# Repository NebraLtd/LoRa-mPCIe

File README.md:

# LoRa-mPCIe
Open source mPCIe LoRa® concentrators from Nebra

## Branches

This repo contains a number of branches with different versions of the LoRa mPCIe hardware as set out below.

### Main

The [main branch of this repo](https://github.com/NebraLtd/LoRa-mPCIe) contains the initial design of the SX1302/3 concentrator but it is based on the original version of the Semtech reference design. It is therefore outdated and is here just for reference purposes. **This hardware has not been verified with prototypes. We do not recommend you use this design.**

### v1.1

The [v1.1 branch of this repo](https://github.com/NebraLtd/LoRa-mPCIe/tree/v1.1) is the latest version of the SX1302/3 based LoRa concentrator design, based on the v3 Semtech Corecell reference design.

There are multiple variants (USB/SPI versions, GNSS/no-GNSS versions and different frequency options). Visit the [v1.1 VARIANTS file](https://github.com/NebraLtd/LoRa-mPCIe/blob/v1.1/VARIANTS.md) for more information on the different hardware versions and how to produce them.

### v1.2
The development can be followed on the v1.2 branch but keeping the branch unmerged to master would create issues as branches generally accepted as unstable. Also the design will be ended with v1.2 from various reasons (Branding issues with Semtech, semantic versioning does not work in hardware design as in software development)

The variant files also can be observed in the Output's folder under their respective folders.

Note: Successor of this design will appear soon in another repo.

### 470/433

In the future, we will have our 470 MHz and 433 MHz designs available as well. As the design differs considerably from the 868/915 versions it may be in a separate branch.

## Open Source Hardware Certification

We are proud to announce that the Nebra LoRa mPCIe Concentrator project is certified as Open Source Hardware by the Open Source Hardware Association ([OSHWA](https://www.oshwa.org/)). The registration number for this project is [UK000026](https://certification.oshwa.org/uk000026.html).

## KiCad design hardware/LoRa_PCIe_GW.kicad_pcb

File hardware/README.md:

# LoRa Gateway mini-PCIe Module (SX1302/3) KiCad Open Source Design

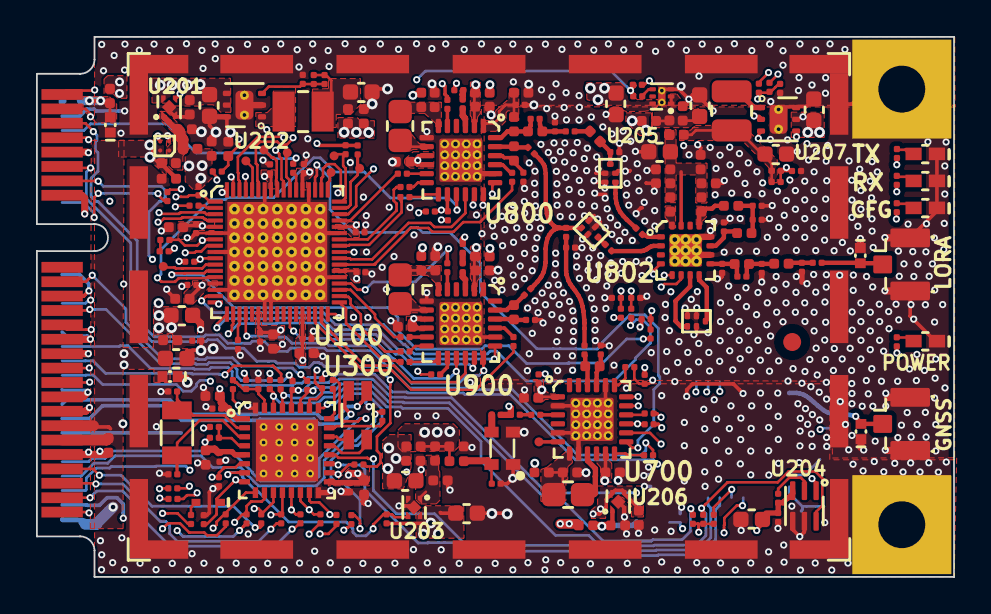
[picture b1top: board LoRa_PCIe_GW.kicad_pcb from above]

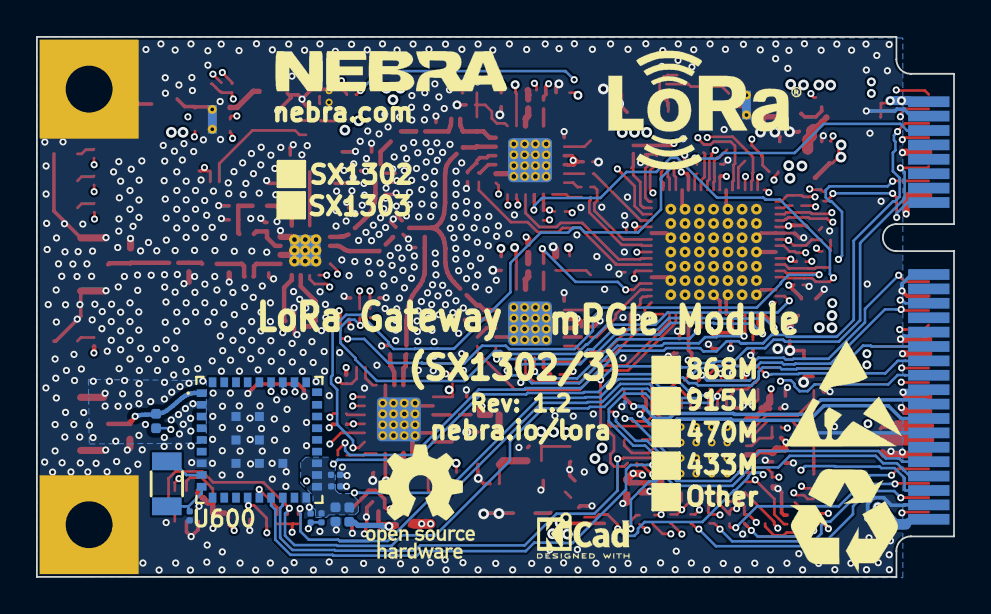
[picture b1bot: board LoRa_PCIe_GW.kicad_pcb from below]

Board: 6 copper layers, 50.9 x 30.0 mm, 269 parts (16 on the bottom side), 190 nets.

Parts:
A1, A2: U.FL; U.FL-R-SMT_Hirose
C100, C102, C103, C105, C106, C107, C108, C109, C110, C600, C602, C838: 100nF; ccer_201_smd_small
C101, C104, C111, C112, C200, C201, C202, C226, C816, C916: 1uF; ccer_402_smd_small
C203: 10uF; ccer_603_smd_small
C204, C822: 4.7uF; ccer_603_smd_small
C205, C207, C211, C212, C222, C305: NC; ccer_603_smd_small
C206, C215, C308: 47uF; ccer_603_smd_small
C208, C210, C216, C220, C221, C312, C818, C918: 100nF; ccer_402_smd_small
C209, C213, C225, C716, C717, C718: NC; ccer_402_smd_small
C214, C223, C309, C708, C710, C711, C712, C713, C827: NC; ccer_201_smd_small
C224: 4.7uF; ccer_402_smd_small
C231: 22pF; ccer_201_smd_small
C301, C307, C310: NC; rlc_402_smd_small
C302, C303, C304, C306, C311: NC; rlc_201_smd_small
C601, C802: 47pF; ccer_201_smd_small
C801: 47nF; ccer_402_smd_small
C804, C831, C832: 3.3pF; ccer_201_smd_small
C805: 5.6pF; ccer_201_smd_small
C806: 39pF; ccer_201_smd_small
C807: 2.2pF; ccer_201_smd_small
C808, C828, C908: 10pF; ccer_201_smd_small
C809, C815, C819, C820, C821, C834: 56pF; ccer_201_smd_small
C811, C812, C911, C912: 3.6pF; ccer_201_smd_small
C817, C917: 470nF; ccer_402_smd_small
C823: 10nF; ccer_402_smd_small
C824: 1nF; ccer_402_smd_small
C825, C826: 100pF; ccer_402_smd_small
C829: 1.3pF; ccer_201_smd_small
C830: 1.5pF; ccer_201_smd_small
C833: 2.7pF; ccer_201_smd_small
D101: BAT54; SOD523
D301: NC; SLP1006P2T
D302: 20V; SLP1006P2T
D600, D801: SLP1006P2T
FB203, FB207, FB208, FB211, FB212, FB302, FB801: Ferrite beads; rlc_402_smd_small
FB205, FB206, FB301: NC; rlc_402_smd_small
Fiducial1: NC; fiducial_mark_signal_top
H1, H2: NC; MountingHole
L200: 2.2uH; LQM2HPN2R2MJ0L
L201: NC; LQM2HPN2R2MJ0L
L300: NC; IND_744232090
L601, L801: 47nH; rlc_402_smd_small
L706, L708, L808, L908: NC; rlc_402_smd_small
L707: NC; rlc_805_smd_small
L803: 2.5nH; rlc_402_smd_small
L804: 4.7nH; rlc_402_smd_small
L806, L906: 12nH; rlc_402_smd_small
L807, L907: 15uH; rlc_805_smd_small
L809: 6.8nH; rlc_402_smd_small
L810: 3.0nH; rlc_402_smd_small
L811: 7.5nH; rlc_402_smd_small
L812: 1.2nH; rlc_402_smd_small
L813, L814: 5.6nH; rlc_402_smd_small
LED1: RED; CD1005-0402-RED
LED2, LED4: GREEN; CD1005-0402
LED3: YELLOW; CD1005-0402-YELLOW
Logo1: NC; Logo_Recycling
Logo2: NC; Logo_ESD
Logo3: NC; Logo_LoRa
Logo4: NC; Logo_KiCad
Logo5: NC; nebra
Logo6: NC; open_source
PCIe_1: NC; PCIeMini-GF-2D-800-1K-S52
Q300, Q600: NC; XTAL_3215_SMD
R101, R103, R107: 47k; rlc_201_smd_small
R102, R301, R302, R308, R309, R316, R317, R318, R319, R326, R331, R332, R333, R334: 100R; rlc_201_smd_small
R104, R105: 680R; rlc_201_smd_small
R106: 820R; rlc_201_smd_small
R108, R600: 10R; rlc_201_smd_small
R109, R110, R111, R112, R113, R114, R115, R120, R121, R122, R123, R124, R125, R200, R602, R815: 0R; rlc_201_smd_small
R116, R117, R203, R206, R601: 4.7k; rlc_201_smd_small
R201: 47K; rlc_201_smd_small
R204, R205, R207, R209, R210, R211, R212, R213, R300, R303, R304, R305, R306, R307, R312, R314, R315, R320, R321, R322, R323, R325, R327, R701, R702, R703, R704, R705, R713: NC; rlc_201_smd_small
R208, R330, R805, R807, R809: 1k; rlc_201_smd_small
R215: NC; rlc_402_smd_small
R221, R222, R813, R913: 0R; rlc_402_smd_small
R231, R232: 182K; rlc_201_smd_small
R801, R901: 220R; rlc_201_smd_small
RF1: Shield Frame; SMS-458F_Shield
RF2: Shield Cover; SMS-458C_Shield_cover
TP1, TP3, TP5, TP6, TP7, TP9, TP10, TP11: NC; PIN_SMD
U100: SX1303; vqfn68_7x7mm
U200: NC; DSBGA-4
U201: 3V3; UDFN4_1x1mm
U202: TPS62260DRV; DRV0006A_V
U203, U206: NC; UDFN4_1x1mm
U204: NC; UDFN-6L_2X2mm
U205: NC; XDFN6_1.2X1.2mm
U207: NC; DRV0006A_V
U300: NC; UFQFPN32_5x5mm
U600: EVA-M8M-0; LGA43R65P9X9_700X700X116
U700: NC; vqfn24_4x4mm
U800, U900: SX1250; vqfn24_4x4mm
U801, U803, U805: SAW Filter; QCS5P_1.4x1.1mm
U802: SKY66423-11; SKY66420_16P_3x3mm
Y800: TCXO; TCXO_2x1_6mm

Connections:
/CONFIG_OK: R105.2, U100.66
/GPIO(9): TP9.1, U100.52
/GPIO(10): R116.1, TP10.1, U100.51
/GPIO(11): R117.1, TP11.1, U100.50
/RADIO_CTRL_(1): TP7.1, U100.11
/RX_ON: R106.2, U100.59
/SCH1/ANT_RF1: C830.2, C831.2, L813.1, U802.9
/SCH1/ANT_RF2: C830.1, C832.1, L813.2, L814.1
/SCH1/ANT_RF3: C833.1, C834.1, L814.2
/SCH1/ANT_RF4: A1.1, C834.2, D801.1
/SCH1/CSD: C819.2, R805.2, U802.4
/SCH1/LNAFLT_RF: U802.8, U803.1
/SCH1/LNAIN_RF: U802.7, U803.4
/SCH1/PA_ON: C821.2, R809.2, U802.5
/SCH1/PA_RF1: L809.1, L810.1, U802.13
/SCH1/PA_RF2: C827.2, C828.2, L810.2, L811.1
/SCH1/PA_RF3: C829.2, L811.2, U802.11
/SCH1/RXTX_SW: C820.2, R807.2, U802.6
/SCH1/RX_RF: C815.2, U802.2
/SCH1/RX_RF1: C815.1, U801.1
/SCH1/RX_RF2: C710.1, C811.1, C911.1, U801.4
/SCH1/SX1250_RFI1_N: C811.2, L806.2, U800.23
/SCH1/SX1250_RFI1_P: C812.2, L806.1, U800.22
/SCH1/SX1250_RFI2_N: C911.2, L906.2, U900.23
/SCH1/SX1250_RFI2_P: C912.2, L906.1, U900.22
/SCH1/SX1261_RFI: C710.2, C711.1, C713.2
/SCH1/SX1261_RFI_N: C711.2, L706.2, U700.22
/SCH1/SX1261_RFI_P: C712.2, L706.1, U700.21
/SCH1/TCXO_32M_O: R701.2, R801.2, R815.1, R901.2
/SCH1/TX_RF: C809.2, U802.1
/SCH1/TX_RF1: C804.2, L801.1, L803.1, U800.24
/SCH1/TX_RF2: C804.1, C805.2, C806.2, L803.2
/SCH1/TX_RF3: C807.2, L804.2, U805.1
/SCH1/TX_RF4: C809.1, U805.4
/SCH1/VR_PA: C801.2, C802.2, L801.2, U800.1
/SCH2/DEBUG_JTCK-SWCLK: R322.2, U300.24
/SCH2/DEBUG_JTMS-SWDIO: R323.2, U300.23
/SCH2/MCU_BOOT0: R304.2, R321.1, R325.1, U300.31
/SCH2/MCU_NRESET: R300.1, R320.1, U300.4
/SCH2/OSC32_IN: C303.1, Q300.2, U300.2
/SCH2/OSC32_OUT: C304.2, Q300.1, U300.3
/SCH2/RADIO_A_CLK_32M_MCU: R303.2, R305.1, U300.6
/SCH2/USB_DN: L300.3, PCIe_1.36
/SCH2/USB_DP: L300.2, PCIe_1.38
/SCH2/VCC5V_IN: D301.1, FB301.1, PCIe_1.2
/SCH3/U205_EN: R207.2, U205.4
/SCH3/U206_EN: R204.2, U207.4
/SCH4/GNSS_RF: A2.1, D600.1, L601.2, U600.1
/TX_ON: R104.2, U100.63
GND: A1.2, A1.3, A2.2, A2.3, C101.1, C102.1, C103.1, C104.1, C105.1, C106.1, C107.1, C108.1, C109.1, C110.1, C111.1, C112.1, C200.2, C201.2, C202.2, C203.2, C204.2, C205.2, C206.2, C207.2, C208.1, C209.2, C210.1, C211.2, C212.2, C213.2, C215.2, C216.1, C220.1, C221.1, C222.2, C223.2, C224.2, C225.2, C226.2, C301.1, C302.2, C303.2, C304.1, C305.2, C306.2, C307.1, C308.2, C309.2, C310.1, C311.2, C312.2, C600.1, C601.1, C602.1, C712.1, C713.1, C716.1, C717.1, C718.1, C801.1, C802.1, C805.1, C807.1, C812.1, C816.1, C817.1, C818.1, C819.1, C820.1, C821.1, C822.1, C823.1, C824.1, C825.1, C826.1, C827.1, C828.1, C829.1, C831.1, C832.2, C833.2, C838.1, C912.1, C916.1, C917.1, C918.1, D301.2, D302.2, D600.2, D801.2, H1.1, H2.1, LED1.2, LED2.2, LED3.2, LED4.2, PCIe_1.4, PCIe_1.9, PCIe_1.15, PCIe_1.18, PCIe_1.21, PCIe_1.26, PCIe_1.27, PCIe_1.29, PCIe_1.34, PCIe_1.35, PCIe_1.37, PCIe_1.40, PCIe_1.43, PCIe_1.50, R101.1, R109.1, R210.1, R212.1, R232.1, R304.1, R305.2, R602.1, RF1.1, U100.6, U100.9, U100.15, U100.24, U100.25, U100.39, U100.46, U100.55, U100.62, U100.69, U200.B1, U201.2, U201.5, U202.2, U202.6, U202.7, U203.2, U203.5, U204.4, U204.5, U205.3, U205.7, U206.2, U206.5, U207.6, U207.7, U300.16, U300.32, U300.33, U600.2, U600.7, U600.18, U600.37, U600.38, U600.39, U600.40, U600.41, U600.42, U600.43, U700.2, U700.5, U700.8, U700.20, U700.25, U800.7, U800.20, U800.25, U801.2, U801.3, U801.5, U802.10, U802.12, U802.17, U803.2, U803.3, U803.5, U805.2, U805.3, U805.5, U900.7, U900.20, U900.25, Y800.1, Y800.2
GNSS_STANDBY: R332.1, U300.25, U600.13
GPIO(6): R326.2, U100.57
HOST_CSN: R103.1, R319.1, U100.1, U300.10
HOST_MISO: R102.2, R317.1, R704.2, U300.12
HOST_MOSI: R318.1, U100.3, U300.13, U700.17
HOST_SCK: R316.1, U100.4, U300.11, U700.18
HOST_UART_RX: R334.1, U300.20, U600.16
HOST_UART_TX: R333.1, U300.19, U600.15
I2C_SCL: R206.1, R308.2, U204.1, U300.29, U600.29
I2C_SDA: R203.1, R309.2, U204.6, U300.30, U600.30
unnamed: C100.2, R108.1
unnamed: C200.1, R200.2, U200.B2, U201.3
unnamed: C202.1, FB207.1, R215.1, U200.A1, U201.1
unnamed: C203.1, C231.2, FB208.1, L200.2, R231.2
unnamed: C211.1, C214.2, FB206.1, L201.2, R211.2
unnamed: C213.1, FB205.1, U203.1
unnamed: C214.1, R211.1, R212.2, U207.3
unnamed: C226.1, FB212.1, R221.1, U206.1
unnamed: C231.1, R231.1, R232.2, U202.3
unnamed: C601.2, L601.1, R600.2
unnamed: C708.1, U700.3
unnamed: C708.2, R701.1
unnamed: C716.2, C718.2, L708.2, R702.1, R703.1, R713.2, U700.1, U700.10, U700.11
unnamed: C717.2, L707.1, L708.1, U700.7
unnamed: C806.1, L804.1
unnamed: C808.1, U800.3
unnamed: C808.2, R801.1
unnamed: C816.2, C818.2, L808.2, R813.2, U800.2, U800.9, U800.10
unnamed: C817.2, L807.1, L808.1, U800.6
unnamed: C838.2, FB801.2, Y800.4
unnamed: C908.1, U900.3
unnamed: C908.2, R901.1
unnamed: C916.2, C918.2, L908.2, R913.2, U900.2, U900.9, U900.10
unnamed: C917.2, L907.1, L908.1, U900.6
unnamed: L200.1, U202.1
unnamed: L201.1, U207.1
unnamed: L300.1, U300.22
unnamed: L300.4, U300.21
unnamed: L707.2, U700.9
unnamed: L807.2, U800.8
unnamed: L812.1, U802.16
unnamed: L907.2, U900.8
unnamed: LED1.1, R104.1
unnamed: LED2.1, R105.1
unnamed: LED3.1, R106.1
unnamed: LED4.1, R208.2
unnamed: PCIe_1.1, R306.1
unnamed: PCIe_1.3, R314.1
unnamed: PCIe_1.5, R307.1
unnamed: PCIe_1.6, R326.1
unnamed: PCIe_1.7, R312.1
unnamed: PCIe_1.11, R315.1
unnamed: PCIe_1.13, R320.2
unnamed: PCIe_1.16, R301.1
unnamed: PCIe_1.19, R330.2
unnamed: PCIe_1.22, R302.1
unnamed: PCIe_1.23, R331.2
unnamed: PCIe_1.25, R332.2
unnamed: PCIe_1.28, R327.1
unnamed: PCIe_1.30, R308.1
unnamed: PCIe_1.31, R333.2
unnamed: PCIe_1.32, R309.1
unnamed: PCIe_1.33, R334.2
unnamed: PCIe_1.44, R322.1
unnamed: PCIe_1.45, R316.2
unnamed: PCIe_1.46, R323.1
unnamed: PCIe_1.47, R317.2
unnamed: PCIe_1.48, R325.2
unnamed: PCIe_1.49, R318.2
unnamed: PCIe_1.51, R319.2
unnamed: Q600.1, R602.2, U600.9
unnamed: Q600.2, U600.8
unnamed: R102.1, U100.2
unnamed: R109.2, U100.20
unnamed: R110.1, U100.44
unnamed: R111.1, U100.45
unnamed: R112.1, U100.49
unnamed: R113.1, U100.41
unnamed: R114.1, U100.48
unnamed: R115.1, U100.43
unnamed: R120.1, U100.35
unnamed: R121.1, U100.36
unnamed: R122.1, U100.38
unnamed: R123.2, U100.32
unnamed: R124.1, U100.37
unnamed: R125.2, U100.34
unnamed: R205.1, U204.2
unnamed: R209.2, R210.2, R213.2, U207.2
unnamed: R704.1, U700.16
unnamed: R705.1, U700.19
unnamed: R815.2, Y800.3
unnamed: TP1.1, U100.64
unnamed: TP3.1, U100.60
unnamed: TP5.1, U100.58
unnamed: TP6.1, U700.6
POWER_EN: R201.2, R301.2, U203.3, U300.7
PPS: R330.1, U100.8, U300.27, U600.31
RADIO_A_CLK_32M: R115.2, R303.1, U800.14
RADIO_A_CLK_O: R114.2, U800.11
RADIO_A_CSN: U100.68, U800.19
RADIO_A_IQ(0): R110.2, U800.13
RADIO_A_IQ(1): R111.2, U800.12
RADIO_A_IQ(2): R112.2, U800.5
RADIO_A_IQ(3): R113.2, U800.21
RADIO_A_MISO: U100.42, U800.16
RADIO_A_MOSI: U100.67, U800.17
RADIO_A_NRESET: U100.13, U800.15
RADIO_A_SCK: U100.65, U800.18
RADIO_B_CLK_32M: R125.1, U900.14
RADIO_B_CLK_O: R124.2, U900.11
RADIO_B_CSN: U100.18, U900.19
RADIO_B_IQ(0): R120.2, U900.13
RADIO_B_IQ(1): R121.2, U900.12
RADIO_B_IQ(2): R122.2, U900.5
RADIO_B_IQ(3): R123.1, U900.21
RADIO_B_MISO: U100.33, U900.16
RADIO_B_MOSI: U100.19, U900.17
RADIO_B_NRESET: U100.28, U900.15
RADIO_B_SCK: U100.21, U900.18
SX1261_BUSY: R306.2, U300.9, U700.14
SX1261_DIO1: R314.2, U100.54, U300.15, U700.13
SX1261_DIO2: R307.2, U700.12
SX1261_NRESET: R315.2, R703.2, U300.18, U700.15
SX1261_NSS: R312.2, R702.2, R705.2, U300.14
SX1302_CSD: R107.1, R204.1, R207.1, R805.1, U100.10
SX1302_GPIO_8: R327.2, U100.53, U300.26
SX1302_PA_ON: R809.1, U100.16
SX1302_PS_EN: R213.1, U100.17
SX1302_RESET: C100.1, D101.1, R101.2, U100.7, U300.8
SX1302_RESET_HOST: D101.2, R302.2
SX1302_RXTX_SW: R807.1, U100.12
VCC3V3_IN: C209.1, C215.1, C216.2, C308.1, C312.1, D302.1, FB203.1, FB302.1, PCIe_1.39, PCIe_1.41, PCIe_1.52, R215.2, R221.2, R222.2, U200.A2
VCCCORE12: C101.2, C102.2, C103.2, C106.2, C108.2, C111.2, C221.2, FB208.2, R200.1, U100.5, U100.23, U100.40, U100.56
VCCGNSS: C224.1, C600.2, C602.2, FB212.2, R600.1, U600.19, U600.20, U600.21
VCCIO33: C104.2, C105.2, C107.2, C109.2, C110.2, C112.2, C220.2, C222.1, C223.1, C301.2, C302.1, C306.1, C307.2, C310.2, C311.1, FB207.2, R103.2, R107.2, R108.2, R116.2, R117.2, R203.2, R205.2, R206.2, R300.2, R321.2, R601.2, U100.14, U100.30, U100.47, U100.61, U204.3, U300.1, U300.5, U300.17
VCC_FEM: C822.2, C823.2, C824.2, C825.2, C826.2, FB206.2, FB211.2, L809.2, L812.2, U802.15
VCC_FEM1: C206.1, C210.2, FB211.1, R222.1, U205.1, U205.2
VCC_MAIN: C201.1, C204.1, C205.1, C207.1, C212.1, C225.1, C305.1, C309.1, FB301.2, FB302.2, R201.1, R208.1, R209.1, U201.4, U202.4, U202.5, U203.4, U205.6, U206.3, U206.4, U207.5
VDD_RADIO: C208.2, FB203.2, FB205.2, FB801.1, R713.1, R813.1, R913.1
~GNSS_RESET~: R331.1, R601.1, U300.28, U600.14

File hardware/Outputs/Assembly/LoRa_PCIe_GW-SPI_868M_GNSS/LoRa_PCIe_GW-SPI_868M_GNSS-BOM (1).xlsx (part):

Reference | Quantity | Value | Footprint | Description | Manufacturer | Part Number | Price[1k] | Supplier Link
A2 A1 | 2.0 | U.FL | LoRa_PCIe_GW:U.FL-R-SMT_Hirose | U.FL (UMCC) Connector Receptacle, Male Pin 50Ohm Surface Mount Solder | Hirose | U.FL-R-SMT-1(80) | 0.65 | https://www.digikey.com/en/products/detail/hirose-electric-c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
C101 C111 C112 C104 C202 C201 C200 C226 C225 C816 C916 | 11.0 | 1uF | LoRa_PCIe_GW:ccer_402_smd_small | 1µF ±20% 10V Ceramic Capacitor X5R 0402 (1005 Metric) | Murata | GRM153R61A105ME95D | 0.038 | https://www.digikey.com/en/products/detail/murata-electronic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
C108 C107 C105 C102 C110 C109 C103 C106 C100 C600 C602 C223 C838 | 13.0 | 100nF | LoRa_PCIe_GW:ccer_201_smd_small | 0.1µF ±10% 16V Ceramic Capacitor X7S 0201 (0603 Metric) | Murata | GRM033C71C104KE14D | 0.01 | https://www.digikey.com/en/products/detail/murata-electronic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
C203 C212 C207 | 3.0 | 10uF | LoRa_PCIe_GW:ccer_603_smd_small | 10µF ±10% 16V Ceramic Capacitor X5R 0603 (1608 Metric) | Murata | GRM188R61C106KAAL | 0.1 | https://www.digikey.com/en/products/detail/murata-electronic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
C204 C206 C822 | 3.0 | 4.7uF | LoRa_PCIe_GW:ccer_603_smd_small | 4.7µF ±10% 16V Ceramic Capacitor X5R 0603 (1608 Metric) | Murata | GRM188R61C475KAAJD | 0.089 | https://www.digikey.com/en/products/detail/murata-electronic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
C222 | 1.0 | 2.2uF | LoRa_PCIe_GW:ccer_603_smd_small | 2.2µF ±10% 10V Ceramic Capacitor X7R 0603 (1608 Metric) | Murata | GRM188R71A225KE15D | 0.039 | https://www.digikey.com/en/products/detail/murata-electronic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
C224 C213 | 2.0 | 4.7uF | LoRa_PCIe_GW:ccer_402_smd_small | 4.7µF ±20% 6.3V Ceramic Capacitor X5R 0402 (1005 Metric) | Murata | GRM155R60J475ME47D | 0.089 | https://www.digikey.com/en/products/detail/murata-electronic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
C308 | 1.0 | 47uF | LoRa_PCIe_GW:ccer_603_smd_small | Multilayer ceramic capacitors X5R ±20%, 6.3V | Murata | GRM188R60J476ME15D | 0.1 | https://www.digikey.com/en/products/detail/murata-electronic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
C312 C221 C220 C208 C818 C918 | 6.0 | 100nF | LoRa_PCIe_GW:ccer_402_smd_small | Multilayer ceramic capacitors X7R ±10%, 16V | Murata | GMD155R71C104KA11 | 0.01 | https://www.digikey.com/en/products/detail/murata-electronic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
C601 C802 | 2.0 | 47pF | LoRa_PCIe_GW:ccer_201_smd_small | 47pF ±5% 50V Ceramic Capacitor C0G, NP0 0201 (0603 Metric) | Murata | GRM0335C1H470JA01D | 0.0036 | https://www.digikey.com/en/products/detail/murata-electronic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
C801 | 1.0 | 47nF | LoRa_PCIe_GW:ccer_402_smd_small | 0.047µF ±10% 16V Ceramic Capacitor X7R 0402 (1005 Metric) | Murata | GRM155R71C473KA01J | 0.012 | https://www.digikey.com/en/products/detail/murata-electronic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
C804 C832 C831 | 3.0 | 3.3pF | LoRa_PCIe_GW:ccer_201_smd_small | 3.3pF ±0.05pF 50V Ceramic Capacitor C0G, NP0 0201 (0603 Metric) | Murata | GJM0335C1H3R3WB01D | 0.026 | https://www.digikey.com/en/products/detail/murata-electronic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
C805 | 1.0 | 5.6pF | LoRa_PCIe_GW:ccer_201_smd_small | 5.6pF ±0.05pF 50V Ceramic Capacitor C0G, NP0 0201 (0603 Metric) | Murata | GRM0335C1H5R6WA01D | 0.005 | https://www.digikey.com/en/products/detail/murata-electronic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
C806 | 1.0 | 39pF | LoRa_PCIe_GW:ccer_201_smd_small | 39pF ±1% 50V Ceramic Capacitor C0G, NP0 0201 (0603 Metric) | Murata | GRM0335C1H390FA01D | 0.0057 | https://www.digikey.com/en/products/detail/murata-electronic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
C807 | 1.0 | 2.2pF | LoRa_PCIe_GW:ccer_201_smd_small | 2.2pF ±0.05pF 50V Ceramic Capacitor C0G, NP0 0201 (0603 Metric) | Murata | GJM0335C1H2R2WB01D | 0.026 | https://www.digikey.com/en/products/detail/murata-electronic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
C808 C908 C828 | 3.0 | 10pF | LoRa_PCIe_GW:ccer_201_smd_small | 10pF ±1% 50V Ceramic Capacitor C0G, NP0 0201 (0603 Metric) | Murata | GRM0335C1H100FA01 | 0.005 | https://www.digikey.com/en/products/detail/murata-electronic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
C811 C812 C911 C912 | 4.0 | 3.6pF | LoRa_PCIe_GW:ccer_201_smd_small | 3.6pF ±0.05pF 25V Ceramic Capacitor C0G, NP0 0201 (0603 Metric) | Murata | GJM0335C1E3R6WB01J | 0.022 | https://www.digikey.com/en/products/detail/murata-electronic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
C817 C917 | 2.0 | 470nF | LoRa_PCIe_GW:ccer_402_smd_small | 0.47µF ±10% 10V Ceramic Capacitor X5R 0402 (1005 Metric) | Murata | GRM155R61A474KE15D | 0.024 | https://www.digikey.com/en/products/detail/murata-electronic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
C823 | 1.0 | 10nF | LoRa_PCIe_GW:ccer_402_smd_small | 10000pF ±10% 10V Ceramic Capacitor X5R 0402 (1005 Metric) | Murata | GRM155R61A103KA01D | 0.007 | https://www.digikey.com/en/products/detail/murata-electronic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
C824 | 1.0 | 1nF | LoRa_PCIe_GW:ccer_402_smd_small | 1000pF ±10% 16V Ceramic Capacitor X7R 0402 (1005 Metric) | Murata | GRM155R71C102KA01D | 0.007 | https://www.digikey.com/en/products/detail/murata-electronic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
C826 C825 | 2.0 | 100pF | LoRa_PCIe_GW:ccer_402_smd_small | 100pF ±1% 50V Ceramic Capacitor C0G, NP0 0402 (1005 Metric) | Murata | GRM1555C1H101FA01D | 0.016 | https://www.digikey.com/en/products/detail/murata-electronic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
C829 | 1.0 | 1.3pF | LoRa_PCIe_GW:ccer_201_smd_small | 1.3pF ±0.05pF 50V Ceramic Capacitor C0G, NP0 0201 (0603 Metric) | Murata | GJM0335C1H1R3WB01 | 0.02 | https://www.digikey.com/en/products/detail/murata-electronic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
C830 | 1.0 | 1.5pF | LoRa_PCIe_GW:ccer_201_smd_small | 1.5pF ±0.05pF 50V Ceramic Capacitor C0G, NP0 0201 (0603 Metric) | Murata | GJM0335C1H1R5WB01 | 0.026 | https://www.digikey.com/en/products/detail/murata-electronic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
C833 | 1.0 | 2.7pF | LoRa_PCIe_GW:ccer_201_smd_small | 2.7pF ±0.25pF 25V Ceramic Capacitor C0G, NP0 0201 (0603 Metric) | Murata | GJM0335C1E2R7CB01J | 0.008 | https://www.digikey.com/en/products/detail/murata-electronic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
C834 C819 C815 C820 C821 C809 | 6.0 | 56pF | LoRa_PCIe_GW:ccer_201_smd_small | 56pF ±1% 50V Ceramic Capacitor C0G, NP0 0201 (0603 Metric) | Murata | GRM0335C1H560FA01D | 0.0057 | https://www.digikey.com/en/products/detail/murata-electronic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
D101 | 1.0 | BAT54 | LoRa_PCIe_GW:SOD523 | Schottky 200mA (DC) Surface Mount SOD-523 | ON Semiconductor | BAT54XV2T1G | 0.046 | https://www.digikey.com/en/products/detail/on-semiconductor/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
D302 | 1.0 | 20V | LoRa_PCIe_GW:SLP1006P2T | 20V Clamp 4A (8/20µs) Ipp Tvs Diode Surface Mount SLP1006P2T | Semtech | RCLAMP0531T.TCT | 0.39 | https://www.digikey.com/en/products/detail/semtech-corporati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
D600 D801 | 2.0 | ~ | LoRa_PCIe_GW:SLP1006P2T | TVS DIODE 4V 1005 | Murata | LXES15AAA1-153 | 0.046 | https://www.digikey.com/en/products/detail/murata-electronic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
FB302 FB208 FB207 FB212 FB205 FB211 FB801 | 7.0 | Ferrite beads | LoRa_PCIe_GW:rlc_402_smd_small | 10 Ohms @ 100MHz 1 Power Line Ferrite Bead 0402 (1005 Metric) 1A 25mOhm | Murata | BLM15PG100SN1D | 0.027 | https://www.digikey.com/en/products/detail/murata-electronic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
L200 | 1.0 | 2.2uH | LoRa_PCIe_GW:LQM2HPN2R2MJ0L | 2.2µH Shielded Multilayer Inductor 1A 150mOhm Max 1008 (2520 Metric) | Murata | LQM2HPN2R2MJ0L | 0.14 | https://www.digikey.com/en/products/detail/murata-electronic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
L601 L801 | 2.0 | 47nH | LoRa_PCIe_GW:rlc_402_smd_small | 47nH Unshielded Wirewound Inductor 210mA 1.08Ohm Max 0402 (1005 Metric) | Murata | LQW15AN47NJ00D | 0.063 | https://www.digikey.com/en/products/detail/murata-electronic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
L803 | 1.0 | 2.5nH | LoRa_PCIe_GW:rlc_402_smd_small | 2.5nH Unshielded Wirewound Inductor 850mA 50mOhm Max 0402 (1005 Metric) | Murata | LQW15AN2N5C00D | 0.066 | https://www.digikey.com/en/products/detail/murata-electronic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
L804 | 1.0 | 4.7nH | LoRa_PCIe_GW:rlc_402_smd_small | 4.7nH Unshielded Wirewound Inductor 750mA 70mOhm Max 0402 (1005 Metric) | Murata | LQW15AN4N7C00D | 0.066 | https://www.digikey.com/en/products/detail/murata-electronic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
L806 L906 | 2.0 | 12nH | LoRa_PCIe_GW:rlc_402_smd_small | 12nH Unshielded Wirewound Inductor 500mA 140mOhm Max 0402 (1005 Metric) | Murata | LQW15AN12NH00D | 0.066 | https://www.digikey.com/en/products/detail/murata-electronic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
L807 L907 | 2.0 | 15uH | LoRa_PCIe_GW:rlc_805_smd_small | 15µH Shielded Multilayer Inductor 250mA 950mOhm 0805 (2012 Metric) | TDK | MLZ2012M150WTD25 | 0.068 | https://www.digikey.com/en/products/detail/tdk-corporation/M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

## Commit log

2021-02-02 Create initialise
2021-03-11 Initial Design Rev:1.0
2021-04-13 Updates according to Corecell_V3 Reference design.
2021-07-29 Added BOM and position files for US915MHz variant
2021-07-29 Corrected quantity field for U801, U805
2021-07-30 Create init
2021-07-31 Added BOM for non GNSS variants. Few part numbers corrected in design.
2022-01-22 fix: fix bom quantities on SAW filters
    BOM quantities were incorrect.
2022-01-22 fix: correct SAW filter quantities
    fix quantities
2022-08-03 Finished routing. Still needs work for DRC errors.
2022-08-03 Deleted old KiCad v5 files
2022-08-03 Fixed branding issues on the back side
2022-08-04 Fixed DRC errors and warnings. Improved manufacturing quality.
2022-08-05 Fixed couple of IO position issues. Controlled everything again.
2022-08-05 Fixed ERC and Schematic to Layout parity errors.
2022-08-25 Updated README for the v1.2 branch.
